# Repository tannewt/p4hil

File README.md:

# P4HIL

An ESP32-P4 hardware-in-the-loop test fixture. A development board drops into
the socket area, and the fixture drives its pins, powers it, measures what it
draws, and exports its USB over the network so a machine anywhere can use it.

KiCad 9 source, 4 layers, 81.28 x 60.96 mm (3.2 x 2.4 in).

## Firmware

The firmware lives in a separate repository:

- [adafruit/esp-usbip-bridge](https://github.com/adafruit/esp-usbip-bridge),
  built with the `p4hil` board profile

It pulls in [adafruit/esp-harness](https://github.com/adafruit/esp-harness) for
SCPI pin and bus control, and
[adafruit/esp-perfetto-logic](https://github.com/adafruit/esp-perfetto-logic)
for logic capture.

## First power-up

Boards arrive with empty flash. Plug the USB-C connector into a host and the
board powers up, finds no application and reboots, so its USB serial device
appears and disappears every few seconds. That is what an unprogrammed board
looks like, not a fault.

The USB-A host ports sit behind load switches the firmware controls, so they
stay dark until something turns them on. There is nothing to diagnose if the
downstream power LED is off on a board you have not flashed yet.

Build once and flash each board in turn:

```bash
./scripts/build-board.sh p4hil build
./scripts/build-board.sh p4hil flash /dev/serial/by-id/usb-Espressif_USB_JTAG_serial_debug_unit_AA:BB:CC:DD:EE:FF-if00
```

The trailing field is the board's MAC address, so the `by-id` path names one
specific board. Prefer it over `ttyACM0` when more than one is attached, since
the numbering moves around between reboots.

After flashing, the board takes a DHCP address over Ethernet and advertises
itself, so you do not need to know the address in advance:

```bash
avahi-browse -rtp _usbip._tcp
```

## What is on the board

| Function | Part |
|---|---|
| MCU | ESP32-P4NRW32, 32 MB in-package PSRAM |
| Flash | W25Q128JVS, 16 MB |
| Ethernet | IP101GR PHY, HanRun HR911105A magjack |
| USB host | CH334F 4-port hub, stacked USB-A plus a 2x5 header |
| USB device | USB-C, full speed, console and power in |
| Current sense | INA219 across a 0.1 ohm shunt on the switched host rail |
| IO expanders | 3x PI4IOE5V9535 at 0x20, 0x21, 0x22 |
| Host power | 2x MT9700/SY6280 load switches, software controlled |
| Misc | WS2812B, STEMMA QT, reset and boot buttons |

## The DUT socket

There is one fixed 20-pin row along the bottom edge and six 19-pin rows stacked
above it at 0.1 inch intervals. All six upper rows carry the same 19 signals, so
you populate only the row that matches the board you want to test.

| Row | Spacing | Silkscreen | Fits |
|---|---|---|---|
| 0 | 0.5" | Trinket | Trinket |
| 1 | 0.6" | QTPy/XIAO/ProMicro | QT Py, XIAO, Pro Micro, Nano |
| 2 | 0.7" | Pico | Raspberry Pi Pico |
| 3 | 0.8" | Feather | any Feather |
| 4 | 0.9" | ESP DevKit | ESP32-S3 DevKitC |
| 5 | 1.0" | ESP32 DevKit | ESP32 DevKitC |

Devices are right-aligned against the `<Start Here` mark on the bottom row.
Marks along the bottom edge show how far each form factor reaches.

Arduino Uno is handled separately on the back of the board: J4 and J2 for the
digital headers, J9 for the analog header. The Uno power header is deliberately
skipped.

## Before you populate headers

**Boards arrive with no DUT headers fitted.** They are through-hole, and which
row you solder is up to you.

Two things worth knowing before you do:

- No position on either DUT row carries power or ground. All 39 are signal lines
  running to ESP32-P4 GPIO.
- The 39 series parts named `R_Protect` in the schematic are 0 ohm in the BOM.

So work out where your device's power pins land before soldering, and leave
those positions unpopulated. A 5 V pin such as a Pico's VBUS would otherwise sit
directly on a 3.3 V GPIO. Ground is shared through the USB cable when the device
is plugged into one of the fixture's own USB-A ports, which is also how the
fixture power-cycles it and measures its current.

## Ordering

`jlcpcb/production_files/` has the gerbers, BOM and CPL as submitted. The CPL
places surface-mount parts only, which is why the DUT headers are unpopulated.

## Repository layout

```
p4hil.kicad_pro / .kicad_sch / .kicad_pcb   top level design
dut.kicad_sch                               DUT headers and pull network
ethernet.kicad_sch                          IP101GR and magjack
usb_host.kicad_sch                          CH334F hub, load switches, INA219
usb_device.kicad_sch                        USB-C
power_options.kicad_sch                     regulators
p4.kicad_sch                                ESP32-P4, flash, crystal
jlcpcb/                                     production output
```

Symbol and footprint libraries come from the `chickadee-libs` and
`kicad-libraries` submodules.

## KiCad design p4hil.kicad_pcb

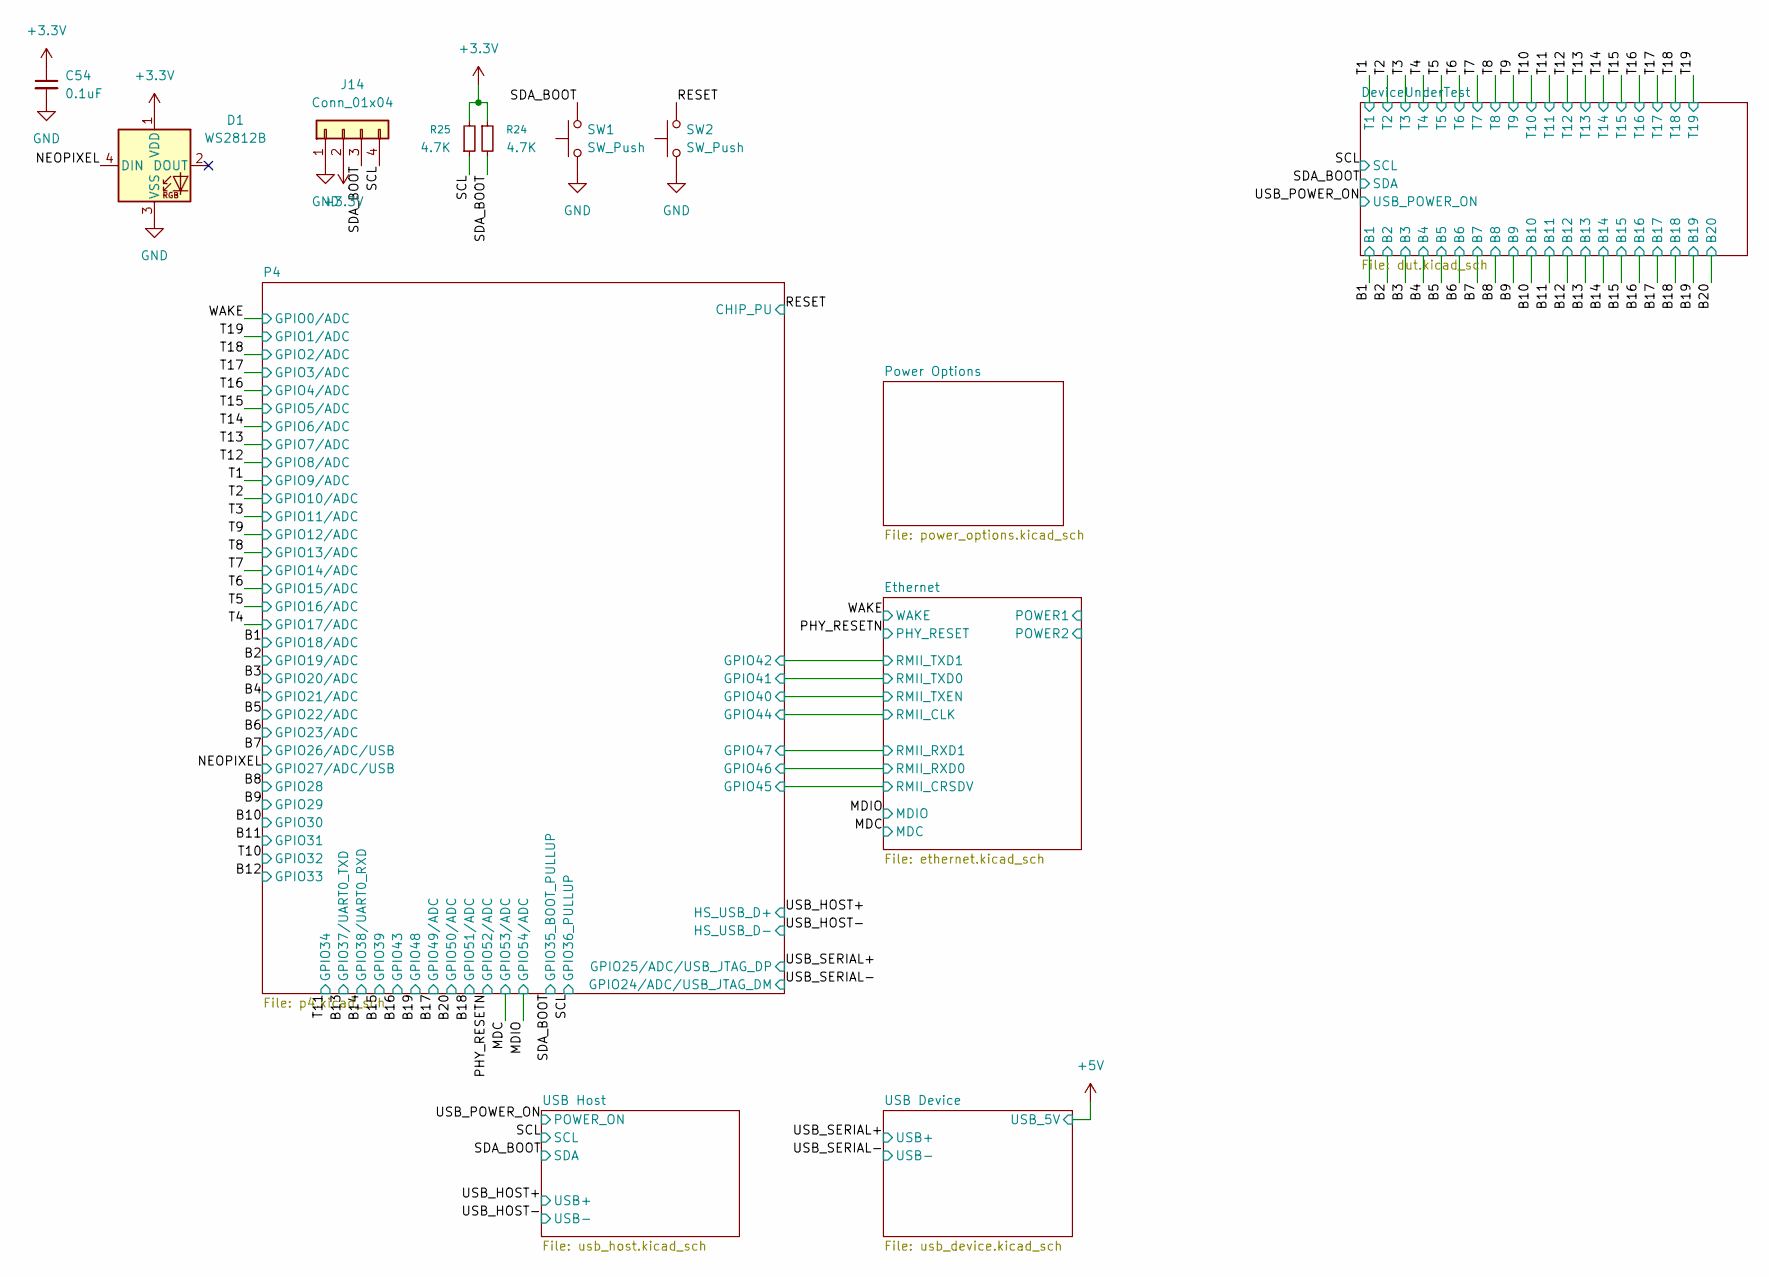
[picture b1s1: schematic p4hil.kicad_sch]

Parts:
C54: 0.1uF; C_0402_1005Metric
D1: WS2812B; WS2812B-4020
J14: Conn_01x04; JST_SH_SM04B-SRSS-TB_1x04-1MP_P1.00mm_Horizontal
R24, R25: 4.7K; R_0402_1005Metric
SW1, SW2: SW_Push; SW_Push_1P1T-MP_NO_Horizontal_Alps_SKRTLAE010

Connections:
+3.3V: C54.1, D1.1 (VDD), J14.2, R24.1, R25.2; also elsewhere on the board
/NEOPIXEL: D1.4 (DIN); also elsewhere on the board
/RESET: SW2.2; also elsewhere on the board
/SCL: J14.4, R25.1; also elsewhere on the board
/SDA_BOOT: J14.3, R24.2, SW1.2; also elsewhere on the board
GND: C54.2, D1.3 (VSS), J14.1, SW1.1, SW2.1; also elsewhere on the board

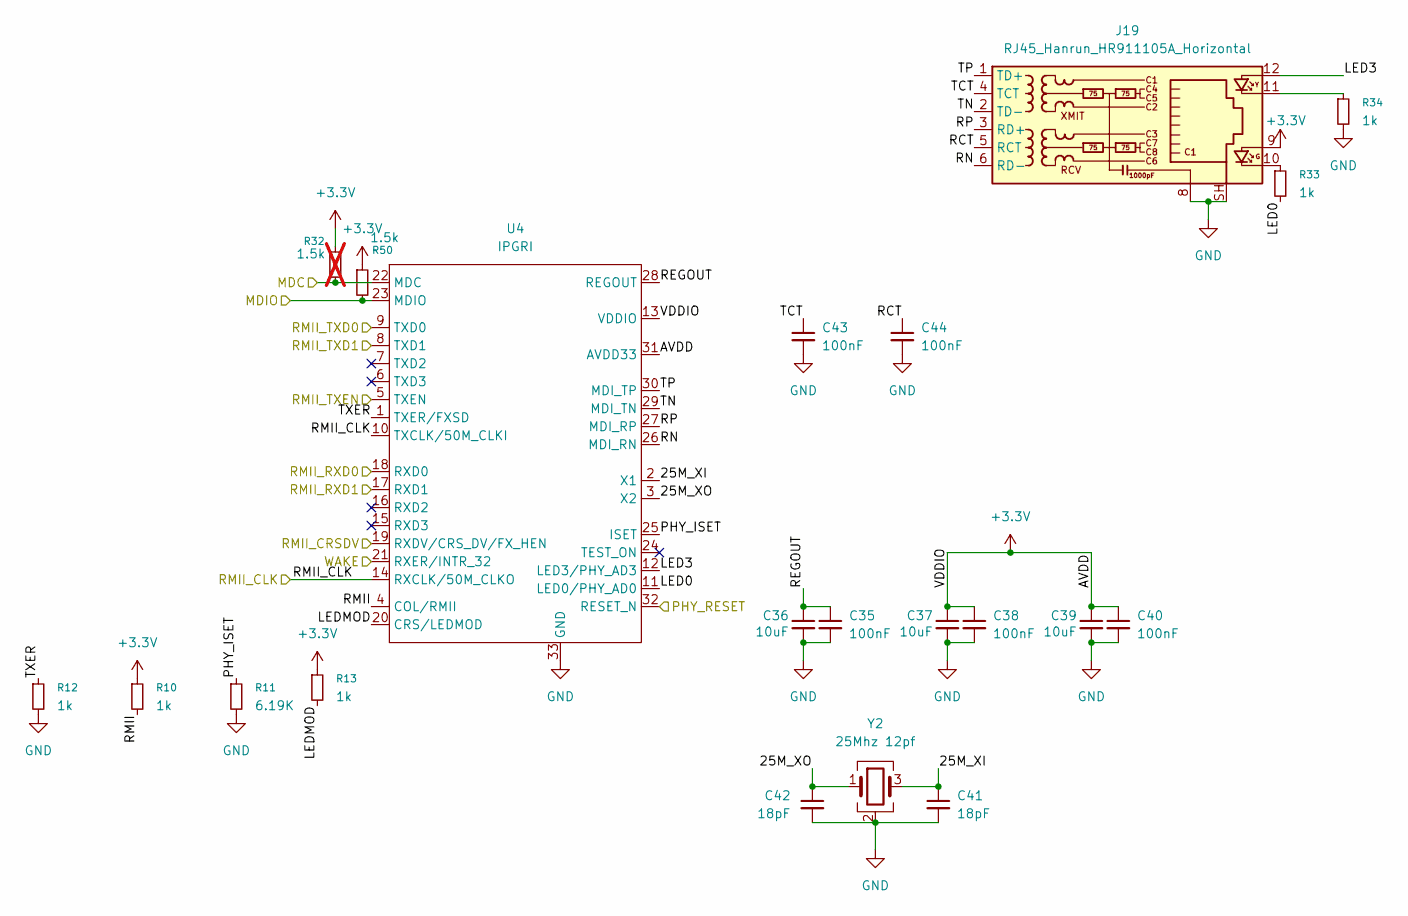
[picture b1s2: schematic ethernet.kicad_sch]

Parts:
C35, C38, C40, C43, C44: 100nF; C_0402_1005Metric
C36, C37, C39: 10uF; C_0603_1608Metric
C41, C42: 18pF; C_0402_1005Metric
J19: RJ45_Hanrun_HR911105A_Horizontal
R10, R12, R13, R33, R34: 1k; R_0402_1005Metric
R11: 6.19K; R_0402_1005Metric
R32: 1.5k; R_0402_1005Metric; not fitted
R50: 1.5k; R_0402_1005Metric
U4: IPGRI; QFN-32-1EP_4x4mm_P0.4mm_EP2.65x2.65mm
Y2: 25Mhz 12pf; Crystal_SMD_3225-4Pin_3.2x2.5mm

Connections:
+3.3V: C37.1, C38.1, C39.1, C40.1, J19.9, R10.1, R13.1, R32.1, R50.1, U4.13 (VDDIO), U4.31 (AVDD33); also elsewhere on the board
/Ethernet/25M_XI: C41.1, U4.2 (X1), Y2.3
/Ethernet/25M_XO: C42.1, U4.3 (X2), Y2.1
/Ethernet/LED0: R33.2, U4.11 (LED0/PHY_AD0)
/Ethernet/LED3: J19.12, U4.12 (LED3/PHY_AD3)
/Ethernet/LEDMOD: R13.2, U4.20 (CRS/LEDMOD)
/Ethernet/PHY_ISET: R11.1, U4.25 (ISET)
/Ethernet/RCT: C44.1, J19.5 (RCT)
/Ethernet/REGOUT: C35.1, C36.1, U4.28 (REGOUT)
/Ethernet/RMII: R10.2, U4.4 (COL/RMII)
/Ethernet/RMII_CLK: U4.10 (TXCLK/50M_CLKI), U4.14 (RXCLK/50M_CLKO); also elsewhere on the board
/Ethernet/RMII_CRSDV: U4.19 (RXDV/CRS_DV/FX_HEN); also elsewhere on the board
/Ethernet/RMII_RXD0: U4.18 (RXD0); also elsewhere on the board
/Ethernet/RMII_RXD1: U4.17 (RXD1); also elsewhere on the board
/Ethernet/RMII_TXD0: U4.9 (TXD0); also elsewhere on the board
/Ethernet/RMII_TXD1: U4.8 (TXD1); also elsewhere on the board
/Ethernet/RMII_TXEN: U4.5 (TXEN); also elsewhere on the board
/Ethernet/RN: J19.6 (RD-), U4.26 (MDI_RN)
/Ethernet/RP: J19.3 (RD+), U4.27 (MDI_RP)
/Ethernet/TCT: C43.1, J19.4 (TCT)
/Ethernet/TN: J19.2 (TD-), U4.29 (MDI_TN)
/Ethernet/TP: J19.1 (TD+), U4.30 (MDI_TP)
/Ethernet/TXER: R12.1, U4.1 (TXER/FXSD)
/MDC: R32.2, U4.22 (MDC); also elsewhere on the board
/MDIO: R50.2, U4.23 (MDIO); also elsewhere on the board
/PHY_RESETN: U4.32 (RESET_N); also elsewhere on the board
/WAKE: U4.21 (RXER/INTR_32); also elsewhere on the board
GND: C35.2, C36.2, C37.2, C38.2, C39.2, C40.2, C41.2, C42.2, C43.2, C44.2, J19.8, J19.SH, R11.2, R12.2, R34.2, U4.33 (GND), Y2.2 (G), Y2.4 (G); also elsewhere on the board
unnamed: J19.10, R33.1
unnamed: J19.11, R34.1

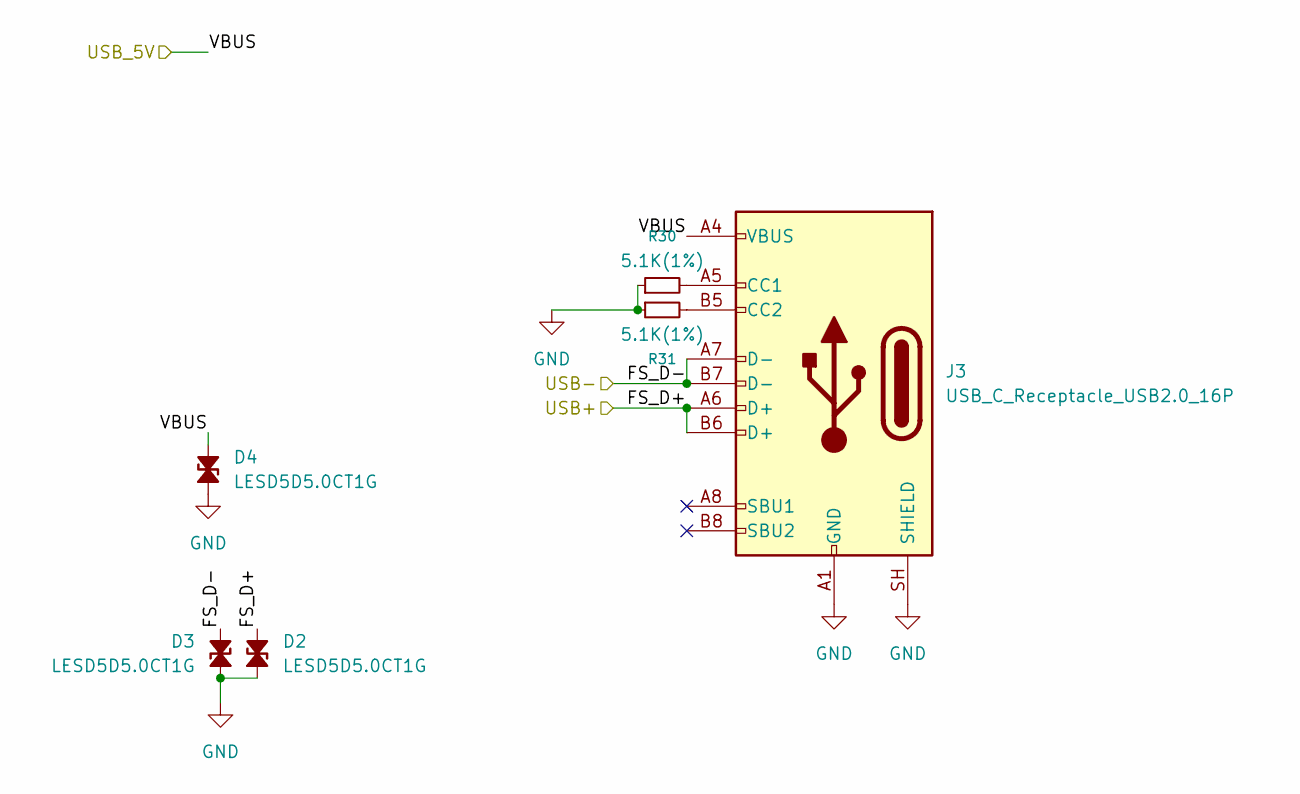
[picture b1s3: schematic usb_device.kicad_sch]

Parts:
D2, D3, D4: LESD5D5.0CT1G; D_SOD-523
J3: USB_C_Receptacle_USB2.0_16P; USB_C_Receptacle_HRO_TYPE-C-31-M-31
R30, R31: 5.1K(1%); R_0402_1005Metric

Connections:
+5V: D4.2 (A2), J3.A4 (VBUS), J3.A9 (VBUS), J3.B4 (VBUS), J3.B9 (VBUS); also elsewhere on the board
/USB_SERIAL+: D2.2 (A2), J3.A6 (D+), J3.B6 (D+); also elsewhere on the board
/USB_SERIAL-: D3.2 (A2), J3.A7 (D-), J3.B7 (D-); also elsewhere on the board
GND: D2.1 (A1), D3.1 (A1), D4.1 (A1), J3.A1 (GND), J3.A12 (GND), J3.B1 (GND), J3.B12 (GND), J3.SH (SHIELD), R30.1, R31.1; also elsewhere on the board
unnamed: J3.A5 (CC1), R30.2
unnamed: J3.B5 (CC2), R31.2

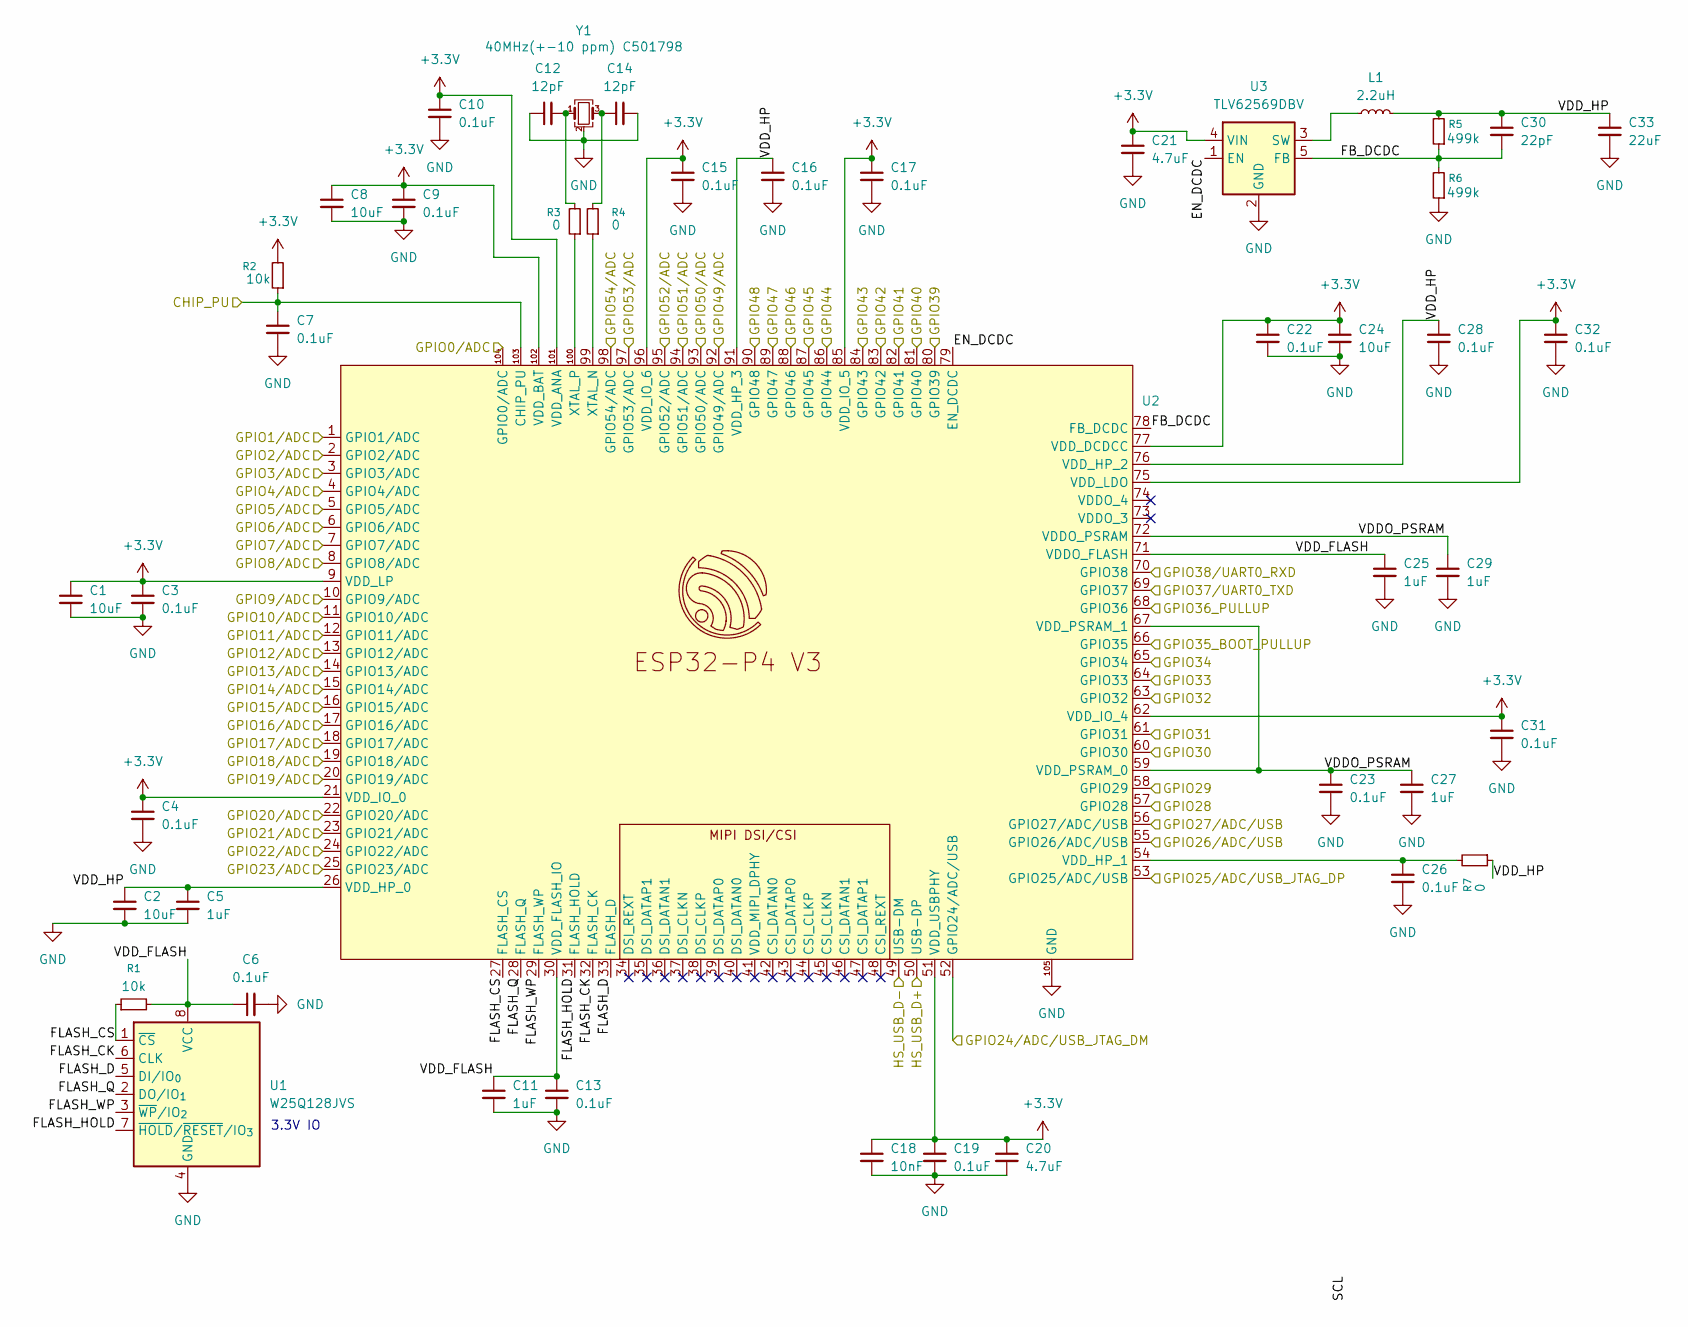
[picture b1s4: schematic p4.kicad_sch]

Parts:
C1, C2, C8, C24: 10uF; C_0603_1608Metric
C3, C4, C6, C7, C9, C10, C13, C15, C16, C17, C19, C22, C23, C26, C28, C31, C32: 0.1uF; C_0402_1005Metric
C5, C11, C25, C27, C29: 1uF; C_0402_1005Metric
C12, C14: 12pF; C_0402_1005Metric
C18: 10nF; C_0402_1005Metric
C20, C21: 4.7uF; C_0402_1005Metric
C30: 22pF; C_0402_1005Metric
C33: 22uF; C_0603_1608Metric
L1: 2.2uH; L_1008_2520Metric
R1, R2: 10k; R_0402_1005Metric
R3, R4, R7: 0; R_0402_1005Metric
R5, R6: 499k; R_0402_1005Metric
U1: W25Q128JVS; WSON-8-1EP_6x5mm_P1.27mm_EP3.4x4.3mm
U2: ESP32-P4
U3: TLV62569DBV; SOT-23-5
Y1: 40MHz(+-10 ppm) C501798; Crystal_SMD_2016-4Pin_2.0x1.6mm

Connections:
+3.3V: C1.1, C3.1, C4.1, C8.1, C9.1, C10.1, C15.1, C17.1, C18.1, C19.1, C20.1, C21.1, C22.1, C24.1, C31.1, C32.1, R2.2, U2.9 (VDD_LP), U2.21 (VDD_IO_0), U2.51 (VDD_USBPHY), U2.62 (VDD_IO_4), U2.75 (VDD_LDO), U2.77 (VDD_DCDCC), U2.85 (VDD_IO_5), U2.96 (VDD_IO_6), U2.101 (VDD_ANA), U2.102 (VDD_BAT), U3.4 (VIN); also elsewhere on the board
/B1: U2.19 (GPIO18/ADC); also elsewhere on the board
/B2: U2.20 (GPIO19/ADC); also elsewhere on the board
/B3: U2.22 (GPIO20/ADC); also elsewhere on the board
/B4: U2.23 (GPIO21/ADC); also elsewhere on the board
/B5: U2.24 (GPIO22/ADC); also elsewhere on the board
/B6: U2.25 (GPIO23/ADC); also elsewhere on the board
/B7: U2.55 (GPIO26/ADC/USB); also elsewhere on the board
/B8: U2.57 (GPIO28); also elsewhere on the board
/B9: U2.58 (GPIO29); also elsewhere on the board
/B10: U2.60 (GPIO30); also elsewhere on the board
/B11: U2.61 (GPIO31); also elsewhere on the board
/B12: U2.64 (GPIO33); also elsewhere on the board
/B13: U2.69 (GPIO37); also elsewhere on the board
/B14: U2.70 (GPIO38); also elsewhere on the board
/B15: U2.80 (GPIO39); also elsewhere on the board
/B16: U2.84 (GPIO43); also elsewhere on the board
/B17: U2.92 (GPIO49/ADC); also elsewhere on the board
/B18: U2.94 (GPIO51/ADC); also elsewhere on the board
/B19: U2.90 (GPIO48); also elsewhere on the board
/B20: U2.93 (GPIO50/ADC); also elsewhere on the board
/Ethernet/RMII_CLK: U2.86 (GPIO44); also elsewhere on the board
/Ethernet/RMII_CRSDV: U2.87 (GPIO45); also elsewhere on the board
/Ethernet/RMII_RXD0: U2.88 (GPIO46); also elsewhere on the board
/Ethernet/RMII_RXD1: U2.89 (GPIO47); also elsewhere on the board
/Ethernet/RMII_TXD0: U2.82 (GPIO41); also elsewhere on the board
/Ethernet/RMII_TXD1: U2.83 (GPIO42); also elsewhere on the board
/Ethernet/RMII_TXEN: U2.81 (GPIO40); also elsewhere on the board
/MDC: U2.97 (GPIO53/ADC); also elsewhere on the board
/MDIO: U2.98 (GPIO54/ADC); also elsewhere on the board
/NEOPIXEL: U2.56 (GPIO27/ADC/USB); also elsewhere on the board
/P4/EN_DCDC: U2.79 (EN_DCDC), U3.1 (EN)
/P4/FB_DCDC: C30.2, R5.1, R6.2, U2.78 (FB_DCDC), U3.5 (FB)
/P4/FLASH_CK: U1.6 (CLK), U2.32 (FLASH_CK)
/P4/FLASH_CS: R1.1, U1.1 (~CS), U2.27 (FLASH_CS)
/P4/FLASH_D: U1.5 (DI/IO_{0}), U2.33 (FLASH_D)
/P4/FLASH_HOLD: U1.7 (~HOLD/~RESET/IO_{3}), U2.31 (FLASH_HOLD)
/P4/FLASH_Q: U1.2 (DO/IO_{1}), U2.28 (FLASH_Q)
/P4/FLASH_WP: U1.3 (~WP/IO_{2}), U2.29 (FLASH_WP)
/P4/VDDO_PSRAM: C23.1, C27.1, C29.1, U2.59 (VDD_PSRAM_0), U2.67 (VDD_PSRAM_1), U2.72 (VDDO_PSRAM)
/P4/VDD_FLASH: C6.1, C11.1, C13.1, C25.1, R1.2, U1.8 (VCC), U2.30 (VDD_FLASH_IO), U2.71 (VDDO_FLASH)
/P4/VDD_HP: C2.1, C5.1, C16.1, C28.1, C30.1, C33.1, L1.2, R5.2, R7.1, U2.26 (VDD_HP_0), U2.76 (VDD_HP_2), U2.91 (VDD_HP_3)
/PHY_RESETN: U2.95 (GPIO52/ADC); also elsewhere on the board
/RESET: C7.1, R2.1, U2.103 (CHIP_PU); also elsewhere on the board
/SCL: U2.68 (GPIO36); also elsewhere on the board
/SDA_BOOT: U2.66 (GPIO35); also elsewhere on the board
/T1: U2.10 (GPIO9/ADC); also elsewhere on the board
/T2: U2.11 (GPIO10/ADC); also elsewhere on the board
/T3: U2.12 (GPIO11/ADC); also elsewhere on the board
/T4: U2.18 (GPIO17/ADC); also elsewhere on the board
/T5: U2.17 (GPIO16/ADC); also elsewhere on the board
/T6: U2.16 (GPIO15/ADC); also elsewhere on the board
/T7: U2.15 (GPIO14/ADC); also elsewhere on the board
/T8: U2.14 (GPIO13/ADC); also elsewhere on the board
/T9: U2.13 (GPIO12/ADC); also elsewhere on the board
/T10: U2.63 (GPIO32); also elsewhere on the board
/T11: U2.65 (GPIO34); also elsewhere on the board
/T12: U2.8 (GPIO8/ADC); also elsewhere on the board
/T13: U2.7 (GPIO7/ADC); also elsewhere on the board
/T14: U2.6 (GPIO6/ADC); also elsewhere on the board
/T15: U2.5 (GPIO5/ADC); also elsewhere on the board
/T16: U2.4 (GPIO4/ADC); also elsewhere on the board
/T17: U2.3 (GPIO3/ADC); also elsewhere on the board
/T18: U2.2 (GPIO2/ADC); also elsewhere on the board
/T19: U2.1 (GPIO1/ADC); also elsewhere on the board
/USB_HOST+: U2.50 (USB-DP); also elsewhere on the board
/USB_HOST-: U2.49 (USB-DM); also elsewhere on the board
/USB_SERIAL+: U2.53 (GPIO25/ADC/USB); also elsewhere on the board
/USB_SERIAL-: U2.52 (GPIO24/ADC/USB); also elsewhere on the board
/WAKE: U2.104 (GPIO0/ADC); also elsewhere on the board
GND: C1.2, C2.2, C3.2, C4.2, C5.2, C6.2, C7.2, C8.2, C9.2, C10.2, C11.2, C12.1, C13.2, C14.2, C15.2, C16.2, C17.2, C18.2, C19.2, C20.2, C21.2, C22.2, C23.2, C24.2, C25.2, C26.2, C27.2, C28.2, C29.2, C31.2, C32.2, C33.2, R6.1, U1.4 (GND), U2.105 (GND), U3.2 (GND), Y1.2 (G), Y1.4 (G); also elsewhere on the board
unnamed: C12.2, R3.2, Y1.1
unnamed: C14.1, R4.2, Y1.3
unnamed: C26.1, R7.2, U2.54 (VDD_HP_1)
unnamed: R4.1, U2.99 (XTAL_N)
unnamed: R3.1, U2.100 (XTAL_P)
unnamed: L1.1, U3.3 (SW)

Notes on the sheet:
3.3V IO

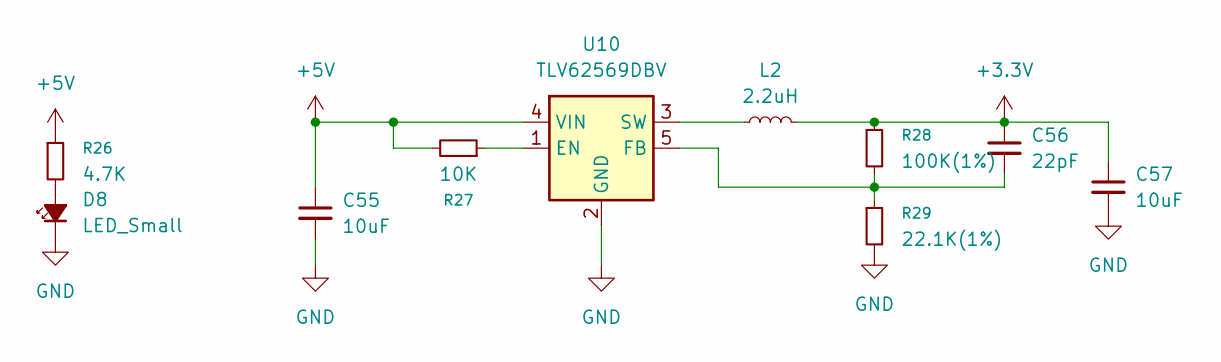
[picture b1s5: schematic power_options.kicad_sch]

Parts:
C55, C57: 10uF; C_0603_1608Metric
C56: 22pF; C_0402_1005Metric
D8: LED_Small; LED_0603_1608Metric
L2: 2.2uH; L_1008_2520Metric
R26: 4.7K; R_0402_1005Metric
R27: 10K; R_0402_1005Metric
R28: 100K(1%); R_0402_1005Metric
R29: 22.1K(1%); R_0402_1005Metric
U10: TLV62569DBV; SOT-23-5

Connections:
+3.3V: C56.1, C57.1, L2.2, R28.1; also elsewhere on the board
+5V: C55.1, R26.1, R27.2, U10.4 (VIN); also elsewhere on the board
GND: C55.2, C57.2, D8.1 (K), R29.2, U10.2 (GND); also elsewhere on the board
unnamed: D8.2 (A), R26.2
unnamed: R27.1, U10.1 (EN)
unnamed: C56.2, R28.2, R29.1, U10.5 (FB)
unnamed: L2.1, U10.3 (SW)

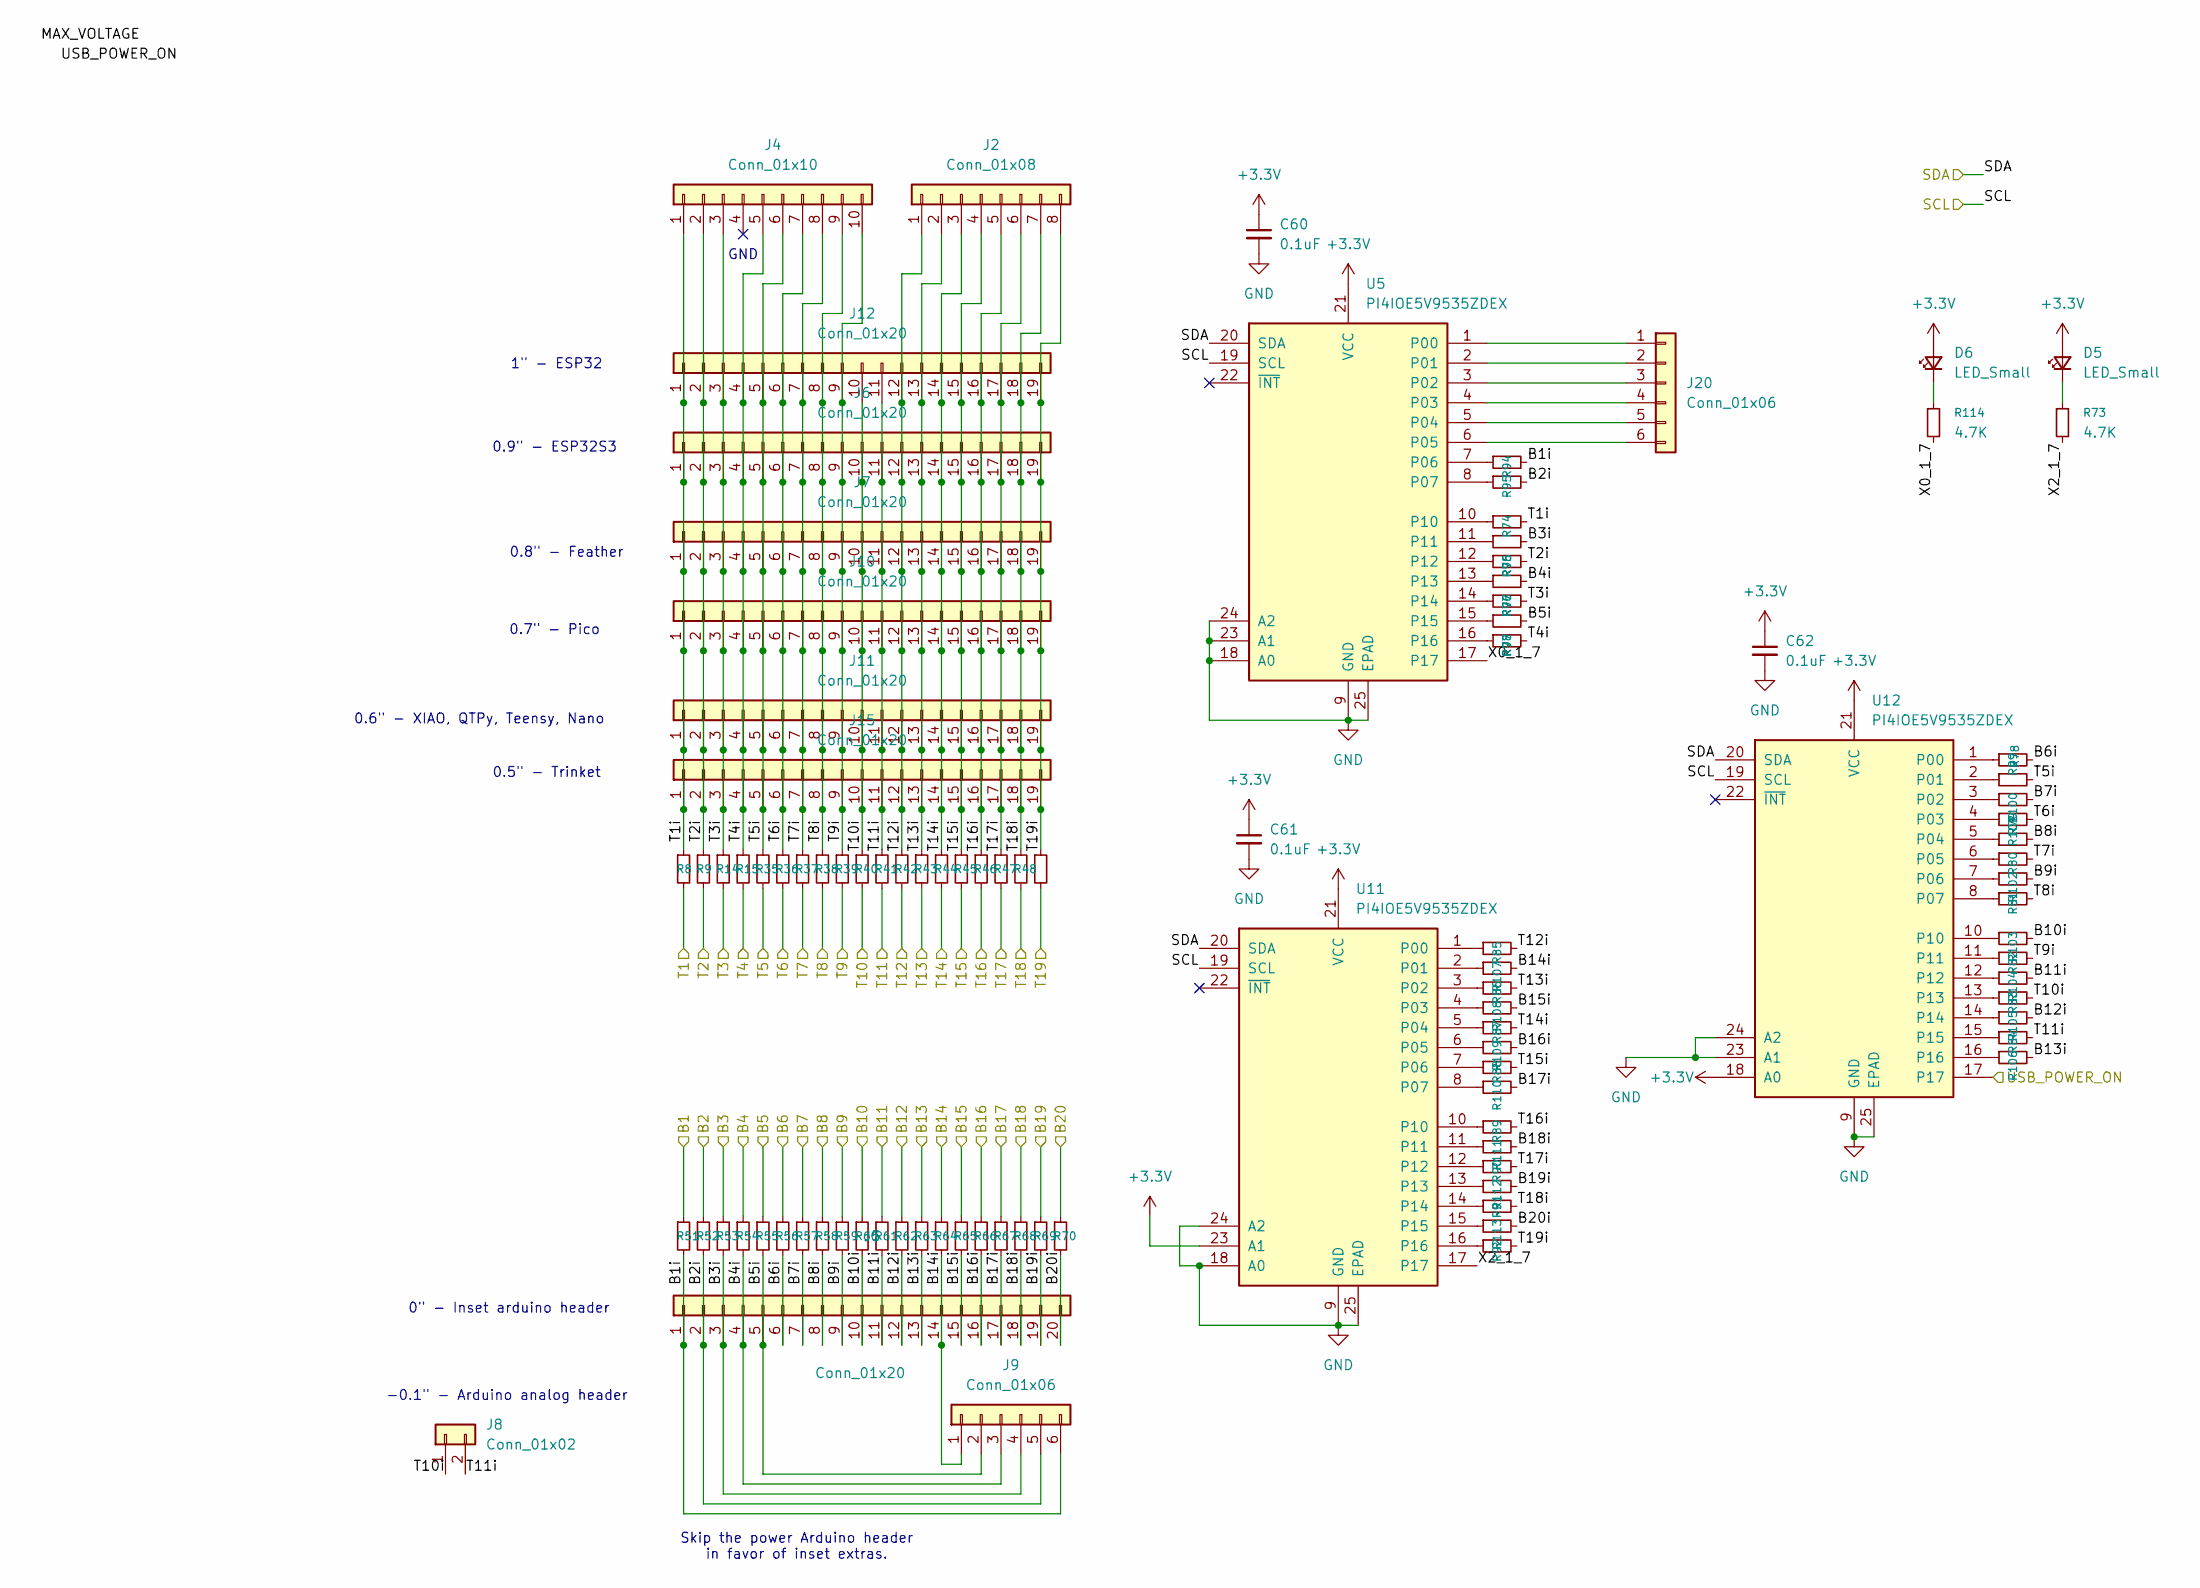
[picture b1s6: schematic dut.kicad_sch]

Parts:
C60, C61, C62: 0.1uF; C_0402_1005Metric
D5, D6: LED_Small; LED_0603_1608Metric
J2: Conn_01x08; PinHeader_1x08_P2.54mm_Vertical
J4: Conn_01x10; PinHeader_1x10_P2.54mm_Vertical
J5: Conn_01x20; PinHeader_1x20_P2.54mm_Vertical
J6, J7, J10, J11, J12, J15: Conn_01x20; PinHeader_1x19_P2.54mm_Vertical
J8: Conn_01x02; PinHeader_1x02_P2.54mm_Vertical
J9, J20: Conn_01x06; PinHeader_1x06_P2.54mm_Vertical
R8, R9, R14, R15, R35, R36, R37, R38, R39, R40, R41, R42, R43, R44, R45, R46, R47, R48, R49, R51, R52, R53, R54, R55, R56, R57, R58, R59, R60, R61, R62, R63, R64, R65, R66, R67, R68, R69, R70: R_Protect; R_0402_1005Metric
R73, R114: 4.7K; R_0402_1005Metric
R74, R75, R76, R77, R78, R79, R80, R81, R82, R83, R84, R85, R86, R87, R88, R89, R90, R91, R92, R94, R95, R96, R97, R98, R99, R100, R101, R102, R103, R104, R105, R106, R107, R108, R109, R110, R111, R112, R113: 2.2K; R_0402_1005Metric
U5, U11, U12: PI4IOE5V9535ZDEX; VQFN-24-1EP_4x4mm_P0.5mm_EP2.45x2.45mm

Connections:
+3.3V: C60.1, C61.1, C62.1, D5.2 (A), D6.2 (A), U5.21 (VCC), U11.21 (VCC), U11.23 (A1), U12.18 (A0), U12.21 (VCC); also elsewhere on the board
/B1: R51.1; also elsewhere on the board
/B2: R52.1; also elsewhere on the board
/B3: R53.1; also elsewhere on the board
/B4: R54.1; also elsewhere on the board
/B5: R55.1; also elsewhere on the board
/B6: R56.1; also elsewhere on the board
/B7: R57.1; also elsewhere on the board
/B8: R58.1; also elsewhere on the board
/B9: R59.1; also elsewhere on the board
/B10: R60.1; also elsewhere on the board
/B11: R61.1; also elsewhere on the board
/B12: R62.1; also elsewhere on the board
/B13: R63.1; also elsewhere on the board
/B14: R64.1; also elsewhere on the board
/B15: R65.1; also elsewhere on the board
/B16: R66.1; also elsewhere on the board
/B17: R67.1; also elsewhere on the board
/B18: R68.1; also elsewhere on the board
/B19: R69.1; also elsewhere on the board
/B20: R70.1; also elsewhere on the board
/DeviceUnderTest/B1i: J5.1, J9.6, R51.2, R94.2
/DeviceUnderTest/B2i: J5.2, J9.5, R52.2, R95.2
/DeviceUnderTest/B3i: J5.3, J9.4, R53.2, R96.2
/DeviceUnderTest/B4i: J5.4, J9.3, R54.2, R97.2
/DeviceUnderTest/B5i: J5.5, J9.2, R55.2, R98.2
/DeviceUnderTest/B6i: J5.6, R56.2, R99.2
/DeviceUnderTest/B7i: J5.7, R57.2, R100.2
/DeviceUnderTest/B8i: J5.8, R58.2, R101.2
/DeviceUnderTest/B9i: J5.9, R59.2, R102.2
/DeviceUnderTest/B10i: J5.10, R60.2, R103.2
/DeviceUnderTest/B11i: J5.11, R61.2, R104.2
/DeviceUnderTest/B12i: J5.12, R62.2, R105.2
/DeviceUnderTest/B13i: J5.13, R63.2, R106.2
/DeviceUnderTest/B14i: J5.14, J9.1, R64.2, R107.2
/DeviceUnderTest/B15i: J5.15, R65.2, R108.2
/DeviceUnderTest/B16i: J5.16, R66.2, R109.2
/DeviceUnderTest/B17i: J5.17, R67.2, R110.2
/DeviceUnderTest/B18i: J5.18, R68.2, R111.2
/DeviceUnderTest/B19i: J5.19, R69.2, R112.2
/DeviceUnderTest/B20i: J5.20, R70.2, R113.2
/DeviceUnderTest/T1i: J4.1, J6.1, J7.1, J10.1, J11.1, J12.1, J15.1, R8.1, R74.2
/DeviceUnderTest/T2i: J4.2, J6.2, J7.2, J10.2, J11.2, J12.2, J15.2, R9.1, R75.2
/DeviceUnderTest/T3i: J4.3, J6.3, J7.3, J10.3, J11.3, J12.3, J15.3, R14.1, R76.2
/DeviceUnderTest/T4i: J4.5, J6.4, J7.4, J10.4, J11.4, J12.4, J15.4, R15.1, R77.2
/DeviceUnderTest/T5i: J4.6, J6.5, J7.5, J10.5, J11.5, J12.5, J15.5, R35.1, R78.2
/DeviceUnderTest/T6i: J4.7, J6.6, J7.6, J10.6, J11.6, J12.6, J15.6, R36.1, R79.2
/DeviceUnderTest/T7i: J4.8, J6.7, J7.7, J10.7, J11.7, J12.7, J15.7, R37.1, R80.2
/DeviceUnderTest/T8i: J4.9, J6.8, J7.8, J10.8, J11.8, J12.8, J15.8, R38.1, R81.2
/DeviceUnderTest/T9i: J4.10, J6.9, J7.9, J10.9, J11.9, J12.9, J15.9, R39.1, R82.2
/DeviceUnderTest/T10i: J6.10, J7.10, J8.1, J10.10, J11.10, J12.10, J15.10, R40.1, R83.2
/DeviceUnderTest/T11i: J6.11, J7.11, J8.2, J10.11, J11.11, J12.11, J15.11, R41.1, R84.2
/DeviceUnderTest/T12i: J2.1, J6.12, J7.12, J10.12, J11.12, J12.12, J15.12, R42.1, R85.2
/DeviceUnderTest/T13i: J2.2, J6.13, J7.13, J10.13, J11.13, J12.13, J15.13, R43.1, R86.2
/DeviceUnderTest/T14i: J2.3, J6.14, J7.14, J10.14, J11.14, J12.14, J15.14, R44.1, R87.2
/DeviceUnderTest/T15i: J2.4, J6.15, J7.15, J10.15, J11.15, J12.15, J15.15, R45.1, R88.2
/DeviceUnderTest/T16i: J2.5, J6.16, J7.16, J10.16, J11.16, J12.16, J15.16, R46.1, R89.2
/DeviceUnderTest/T17i: J2.6, J6.17, J7.17, J10.17, J11.17, J12.17, J15.17, R47.1, R90.2
/DeviceUnderTest/T18i: J2.7, J6.18, J7.18, J10.18, J11.18, J12.18, J15.18, R48.1, R91.2
/DeviceUnderTest/T19i: J2.8, J6.19, J7.19, J10.19, J11.19, J12.19, J15.19, R49.1, R92.2
/DeviceUnderTest/X0_1_7: R114.2, U5.17
/DeviceUnderTest/X2_1_7: R73.2, U11.17
/SCL: U5.19 (SCL), U11.19 (SCL), U12.19 (SCL); also elsewhere on the board
/SDA_BOOT: U5.20 (SDA), U11.20 (SDA), U12.20 (SDA); also elsewhere on the board
/T1: R8.2; also elsewhere on the board
/T2: R9.2; also elsewhere on the board
/T3: R14.2; also elsewhere on the board
/T4: R15.2; also elsewhere on the board
/T5: R35.2; also elsewhere on the board
/T6: R36.2; also elsewhere on the board
/T7: R37.2; also elsewhere on the board
/T8: R38.2; also elsewhere on the board
/T9: R39.2; also elsewhere on the board
/T10: R40.2; also elsewhere on the board
/T11: R41.2; also elsewhere on the board
/T12: R42.2; also elsewhere on the board
/T13: R43.2; also elsewhere on the board
/T14: R44.2; also elsewhere on the board
/T15: R45.2; also elsewhere on the board
/T16: R46.2; also elsewhere on the board
/T17: R47.2; also elsewhere on the board
/T18: R48.2; also elsewhere on the board
/T19: R49.2; also elsewhere on the board
/USB_POWER_ON: U12.17; also elsewhere on the board
GND: C60.2, C61.2, C62.2, U5.9 (GND), U5.18 (A0), U5.23 (A1), U5.24 (A2), U5.25 (EPAD), U11.9 (GND), U11.18 (A0), U11.24 (A2), U11.25 (EPAD), U12.9 (GND), U12.23 (A1), U12.24 (A2), U12.25 (EPAD); also elsewhere on the board
unnamed: D5.1 (K), R73.1
unnamed: D6.1 (K), R114.1
unnamed: J20.1, U5.1 (P00)
unnamed: J20.2, U5.2 (P01)
unnamed: J20.3, U5.3 (P02)
unnamed: J20.4, U5.4 (P03)
unnamed: J20.5, U5.5 (P04)
unnamed: J20.6, U5.6 (P05)
unnamed: R94.1, U5.7 (P06)
unnamed: R95.1, U5.8 (P07)
unnamed: R74.1, U5.10
unnamed: R96.1, U5.11
unnamed: R75.1, U5.12
unnamed: R97.1, U5.13
unnamed: R76.1, U5.14
unnamed: R98.1, U5.15
unnamed: R77.1, U5.16
unnamed: R85.1, U11.1 (P00)
unnamed: R107.1, U11.2 (P01)
unnamed: R86.1, U11.3 (P02)
unnamed: R108.1, U11.4 (P03)
unnamed: R87.1, U11.5 (P04)
unnamed: R109.1, U11.6 (P05)
unnamed: R88.1, U11.7 (P06)
unnamed: R110.1, U11.8 (P07)
unnamed: R89.1, U11.10
unnamed: R111.1, U11.11
unnamed: R90.1, U11.12
unnamed: R112.1, U11.13
unnamed: R91.1, U11.14
unnamed: R113.1, U11.15
unnamed: R92.1, U11.16
unnamed: R99.1, U12.1 (P00)
unnamed: R78.1, U12.2 (P01)
unnamed: R100.1, U12.3 (P02)
unnamed: R79.1, U12.4 (P03)
unnamed: R101.1, U12.5 (P04)
unnamed: R80.1, U12.6 (P05)
unnamed: R102.1, U12.7 (P06)
unnamed: R81.1, U12.8 (P07)
unnamed: R103.1, U12.10
unnamed: R82.1, U12.11
unnamed: R104.1, U12.12
unnamed: R83.1, U12.13
unnamed: R105.1, U12.14
unnamed: R84.1, U12.15
unnamed: R106.1, U12.16

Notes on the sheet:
0" - Inset arduino header
GND
1" - ESP32
-0.1" - Arduino analog header
0.6" - XIAO, QTPy, Teensy, Nano
0.5" - Trinket
0.9" - ESP32S3
0.8" - Feather
0.7" - Pico
Skip the power Arduino header in favor of inset extras.
